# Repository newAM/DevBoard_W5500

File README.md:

## Bear-bones W5500 Development Board

This project is a bear-bones development board for the W5500.  The goal is to allow maximum configurability during prototyping by having only essential components on the board, with the rest of the pins on a 2.54mm header.

## Media

## Project Contents
-  DevBoard_W5500_KiCAD - KiCad PCB and schematic files
-  DevBoard_W5500_Media - photos

## Bill of Materials

| Reference | Value | Package     | Digikey P/N      | Quantity |
| --------- |------ |-------------|------------------|----------|
| U1        | W5500 | LFFP-48 7x7 | 1278-1021-ND     | 1        |
| R1        | 12.4k | 0603        | 311-12.4KHRCT-ND | 1        |
| R2        | 1M    | 0603        | 311-1.0MGRCT-ND  | 1        |
| C1-C6     | 100n  | 0603        | 1276-1012-1-ND   | 6        |
| C6        | 10n   | 0603        | 1276-1921-1-ND   | 1        |
| C7        | 4.7u  | 0603        | 1276-1907-1-ND   | 1        |
| C8-C9     | 18p   | 0603        | 1276-1089-1-ND   | 2        |
| Y1        | 25MHz | 5x3.2mm     | CTX1434CT-ND     | 1        |
| X1-X2     | 1x10  | 2.54mm      |                  | 2        |

## Software Used
- [KiCad](http://kicad-pcb.org/) 5.0.0 release

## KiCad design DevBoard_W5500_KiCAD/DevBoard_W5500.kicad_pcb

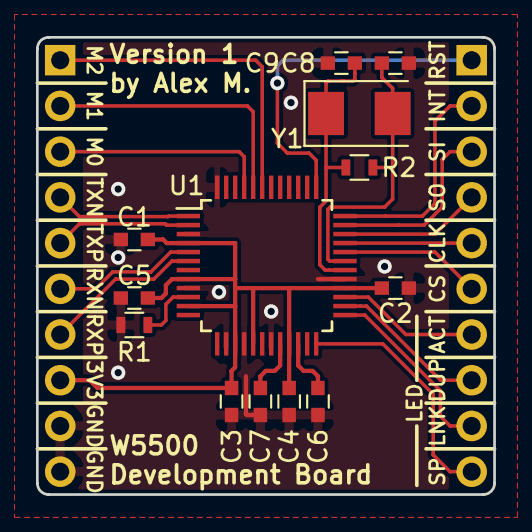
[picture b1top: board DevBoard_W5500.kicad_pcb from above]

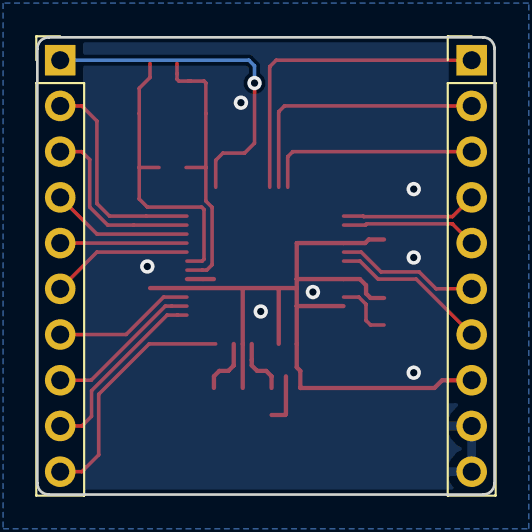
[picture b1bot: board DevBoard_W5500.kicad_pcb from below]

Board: 2 copper layers, 25.4 x 25.4 mm, 15 parts (2 on the bottom side), 24 nets.

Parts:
C1, C2, C3, C4, C5: 100n; C_0603
C6: 10n; C_0603
C7: 4.7u; C_0603
C8, C9: 18p; C_0603
R1: 12.4k; R_0603
R2: 1M; R_0603
U1: W5500; LQFP-48_7x7mm_Pitch0.5mm
X1, X2: Conn_01x10; Pin_Header_Straight_1x10_Pitch2.54mm
Y1: 25MHz; Crystal_SMD_5032-2pin_5.0x3.2mm

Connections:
+3V3: C1.1, C2.1, C3.1, C4.1, C5.1, U1.4, U1.8, U1.11, U1.15, U1.17, U1.21, U1.28, X1.8
/1V2O: C6.1, U1.22
/XCAP: C7.1, U1.20
/XI: C9.1, R2.1, U1.30, Y1.1
/XO: C8.1, R2.2, U1.31, Y1.2
/XRES: R1.1, U1.10
ACTLED: U1.27, X2.7
CS: U1.32, X2.6
DUPLED: U1.26, X2.8
GND: C1.2, C2.2, C3.2, C4.2, C5.2, C6.2, C7.2, C8.2, C9.2, R1.2, U1.3, U1.9, U1.14, U1.16, U1.19, U1.29, U1.48, X1.9, X1.10
INT: U1.36, X2.2
LINKLED: U1.25, X2.9
MISO: U1.34, X2.4
MOSI: U1.35, X2.3
PMODE0: U1.45, X1.3
PMODE1: U1.44, X1.2
PMODE2: U1.43, X1.1
RESET: U1.37, X2.1
RXIN: U1.5, X1.6
RXIP: U1.6, X1.7
SCLK: U1.33, X2.5
SPDLED: U1.24, X2.10
TXON: U1.1, X1.4
TXOP: U1.2, X1.5

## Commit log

2018-09-09 inital commit
2018-09-09 corrected link to photo
2018-09-15 Corrected quanities in BoM
2018-10-06 corrected error in bill of materials
2018-10-06 added photo of finished product
2018-10-06 corrected overlay text for finished PCB
2018-10-06 corrected file extension in README
2021-11-09 Update kicad URL
    https://forum.kicad.info/t/warning-avoid-all-links-to-kicad-pcb-org-use-kicad-org/31521
